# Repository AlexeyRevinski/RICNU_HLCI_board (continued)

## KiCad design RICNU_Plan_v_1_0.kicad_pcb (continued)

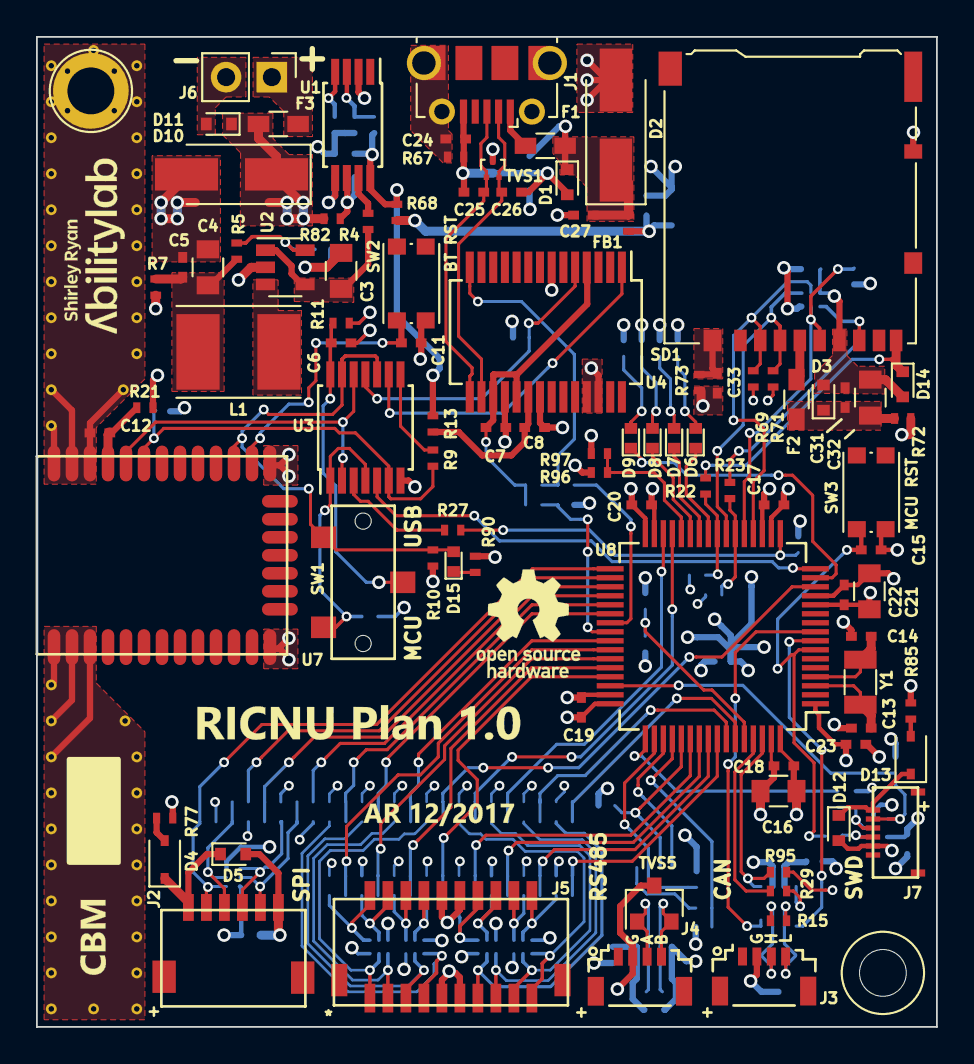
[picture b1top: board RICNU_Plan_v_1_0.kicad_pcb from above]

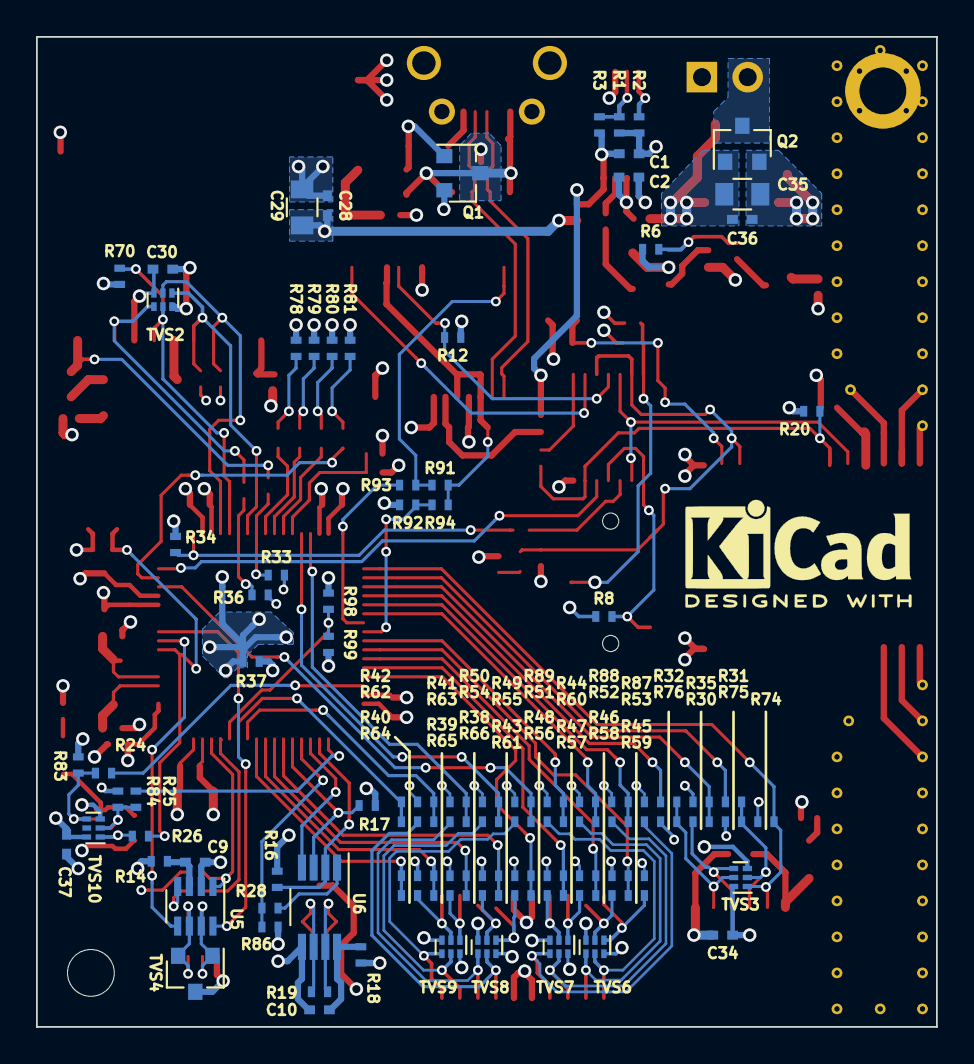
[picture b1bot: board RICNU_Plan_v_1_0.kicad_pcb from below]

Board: 4 copper layers, 50.0 x 55.0 mm, 188 parts (96 on the bottom side), 128 nets.

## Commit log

2017-11-28 First commit - board almost routed
2017-11-29 All nets connected, silkscreen done, via sizes checked
2017-11-29 Re-routed CAN, RS-485, and debug connectors (wrong polarity in all)
2017-12-01 Added connections to monitor power, changed CANSTB MCU pin, moved LED pins around
2017-12-04 had to relocate 4.7uF cap for STM32 based on datasheet info. Experimenting with reset button location
2017-12-06 Design freeze - ordered the board
2018-02-20 Various small changes like comment removal
2018-03-22 Deleting PDFs
2018-03-22 Deleting old files
